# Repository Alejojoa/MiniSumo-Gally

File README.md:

# MiniSumo "Gally"                   
Mini sumo diseñado para competir en la LNR. 
Este repositorio contiene todas las piezas fabricables del Robot, y extras como soportes, versiones no finales del chasis, otros diseños de chasis, etc.

## ⚙️ Características 

- Tamaño: [10x10]
- Peso: [470g]
- Controlador: [Arduino Nano]
- Sensores:
  - Sensores de línea infrarrojos QRE-1113 x 2
  - Sensores JS40F x 4
- Motores: [Motores JSUMO CORE 400RPM]
- Batería: [Tattu 3S 450mAh]

# Pre Render del chasis final del robot.

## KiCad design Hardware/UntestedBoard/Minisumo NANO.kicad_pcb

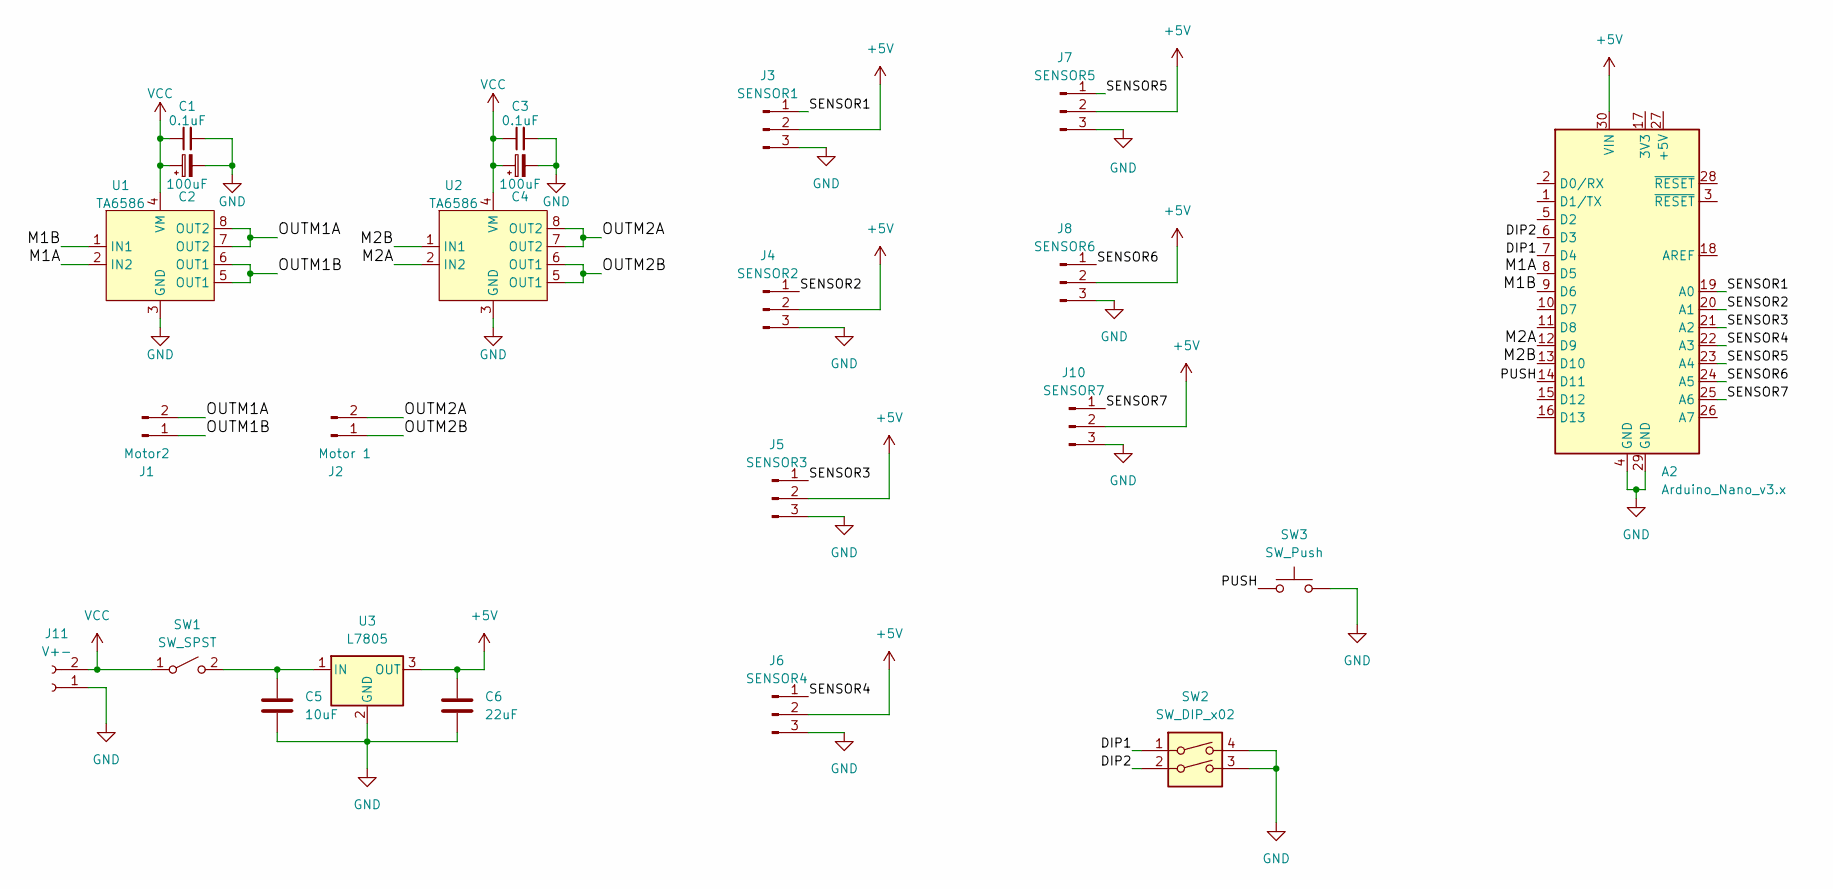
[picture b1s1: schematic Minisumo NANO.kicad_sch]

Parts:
A2: Arduino_Nano_v3.x; Arduino_Nano
C1, C3: 0.1uF; C_0805_2012Metric_Pad1.18x1.45mm_HandSolder
C2, C4: 100uF; CP_Radial_D5.0mm_P2.50mm
C5: 10uF; C_0805_2012Metric_Pad1.18x1.45mm_HandSolder
C6: 22uF; C_0805_2012Metric_Pad1.18x1.45mm_HandSolder
J1: Motor2; JST_XH_B2B-XH-A_1x02_P2.50mm_Vertical
J2: Motor 1; JST_XH_B2B-XH-A_1x02_P2.50mm_Vertical
J3: SENSOR1; PinHeader_1x03_P2.54mm_Vertical
J4: SENSOR2; PinHeader_1x03_P2.54mm_Vertical
J5: SENSOR3; PinHeader_1x03_P2.54mm_Vertical
J6: SENSOR4; PinHeader_1x03_P2.54mm_Vertical
J7: SENSOR5; PinHeader_1x03_P2.54mm_Vertical
J8: SENSOR6; PinHeader_1x03_P2.54mm_Vertical
J10: SENSOR7; PinHeader_1x03_P2.54mm_Vertical
J11: V+-; BORNERA2
SW1: SW_SPST; PinHeader_1x02_P2.54mm_Vertical
SW2: SW_DIP_x02; SW_DIP_SPSTx02_Slide_6.7x6.64mm_W7.62mm_P2.54mm_LowProfile
SW3: SW_Push; SW_PUSH_6mm_H5mm
U1, U2: TA6586; DIP-8_W7.62mm
U3: L7805; TO-220-3_Vertical

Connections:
+5V: A2.30 (VIN), C6.1, J3.2, J4.2, J5.2, J6.2, J7.2, J8.2, J10.2, U3.3 (OUT)
/DIP1: A2.7 (D4), SW2.1
/DIP2: A2.6 (D3), SW2.2
/M1A: A2.8 (D5), U1.2 (IN2)
/M1B: A2.9 (D6), U1.1 (IN1)
/M2A: A2.12 (D9), U2.2 (IN2)
/M2B: A2.13 (D10), U2.1 (IN1)
/OUTM1A: J1.2, U1.7 (OUT2), U1.8 (OUT2)
/OUTM1B: J1.1, U1.5 (OUT1), U1.6 (OUT1)
/OUTM2A: J2.2, U2.7 (OUT2), U2.8 (OUT2)
/OUTM2B: J2.1, U2.5 (OUT1), U2.6 (OUT1)
/PUSH: A2.14 (D11), SW3.1
/SENSOR1: A2.19 (A0), J3.1
/SENSOR2: A2.20 (A1), J4.1
/SENSOR3: A2.21 (A2), J5.1
/SENSOR4: A2.22 (A3), J6.1
/SENSOR5: A2.23 (A4), J7.1
/SENSOR6: A2.24 (A5), J8.1
/SENSOR7: A2.25 (A6), J10.1
GND: A2.4 (GND), A2.29 (GND), C1.2, C2.2, C3.2, C4.2, C5.2, C6.2, J3.3, J4.3, J5.3, J6.3, J7.3, J8.3, J10.3, J11.1, SW2.3, SW2.4, SW3.2, U1.3 (GND), U2.3 (GND), U3.2 (GND)
unnamed: C5.1, SW1.2 (B), U3.1 (IN)
VCC: C1.1, C2.1, C3.1, C4.1, J11.2, SW1.1 (A), U1.4 (VM), U2.4 (VM)

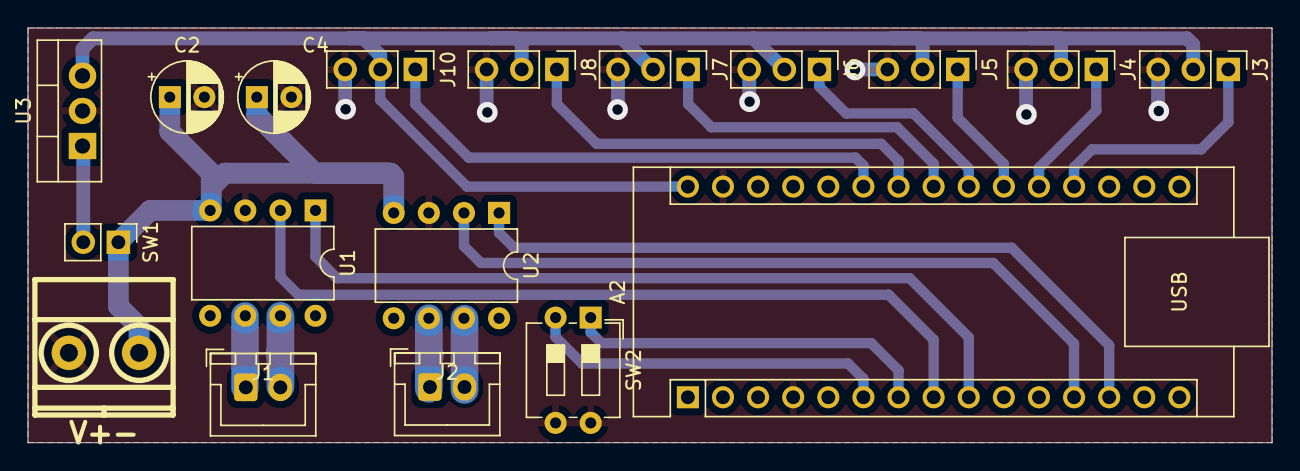
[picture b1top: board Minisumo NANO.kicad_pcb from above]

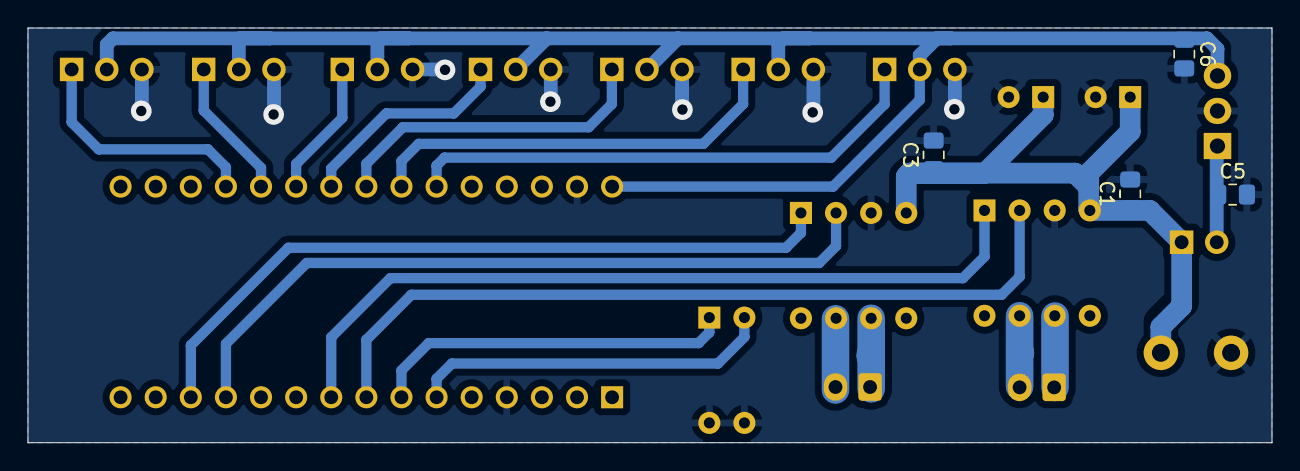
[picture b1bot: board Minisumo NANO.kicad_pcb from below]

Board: 2 copper layers, 90.0 x 30.0 mm, 22 parts (4 on the bottom side), 21 nets.

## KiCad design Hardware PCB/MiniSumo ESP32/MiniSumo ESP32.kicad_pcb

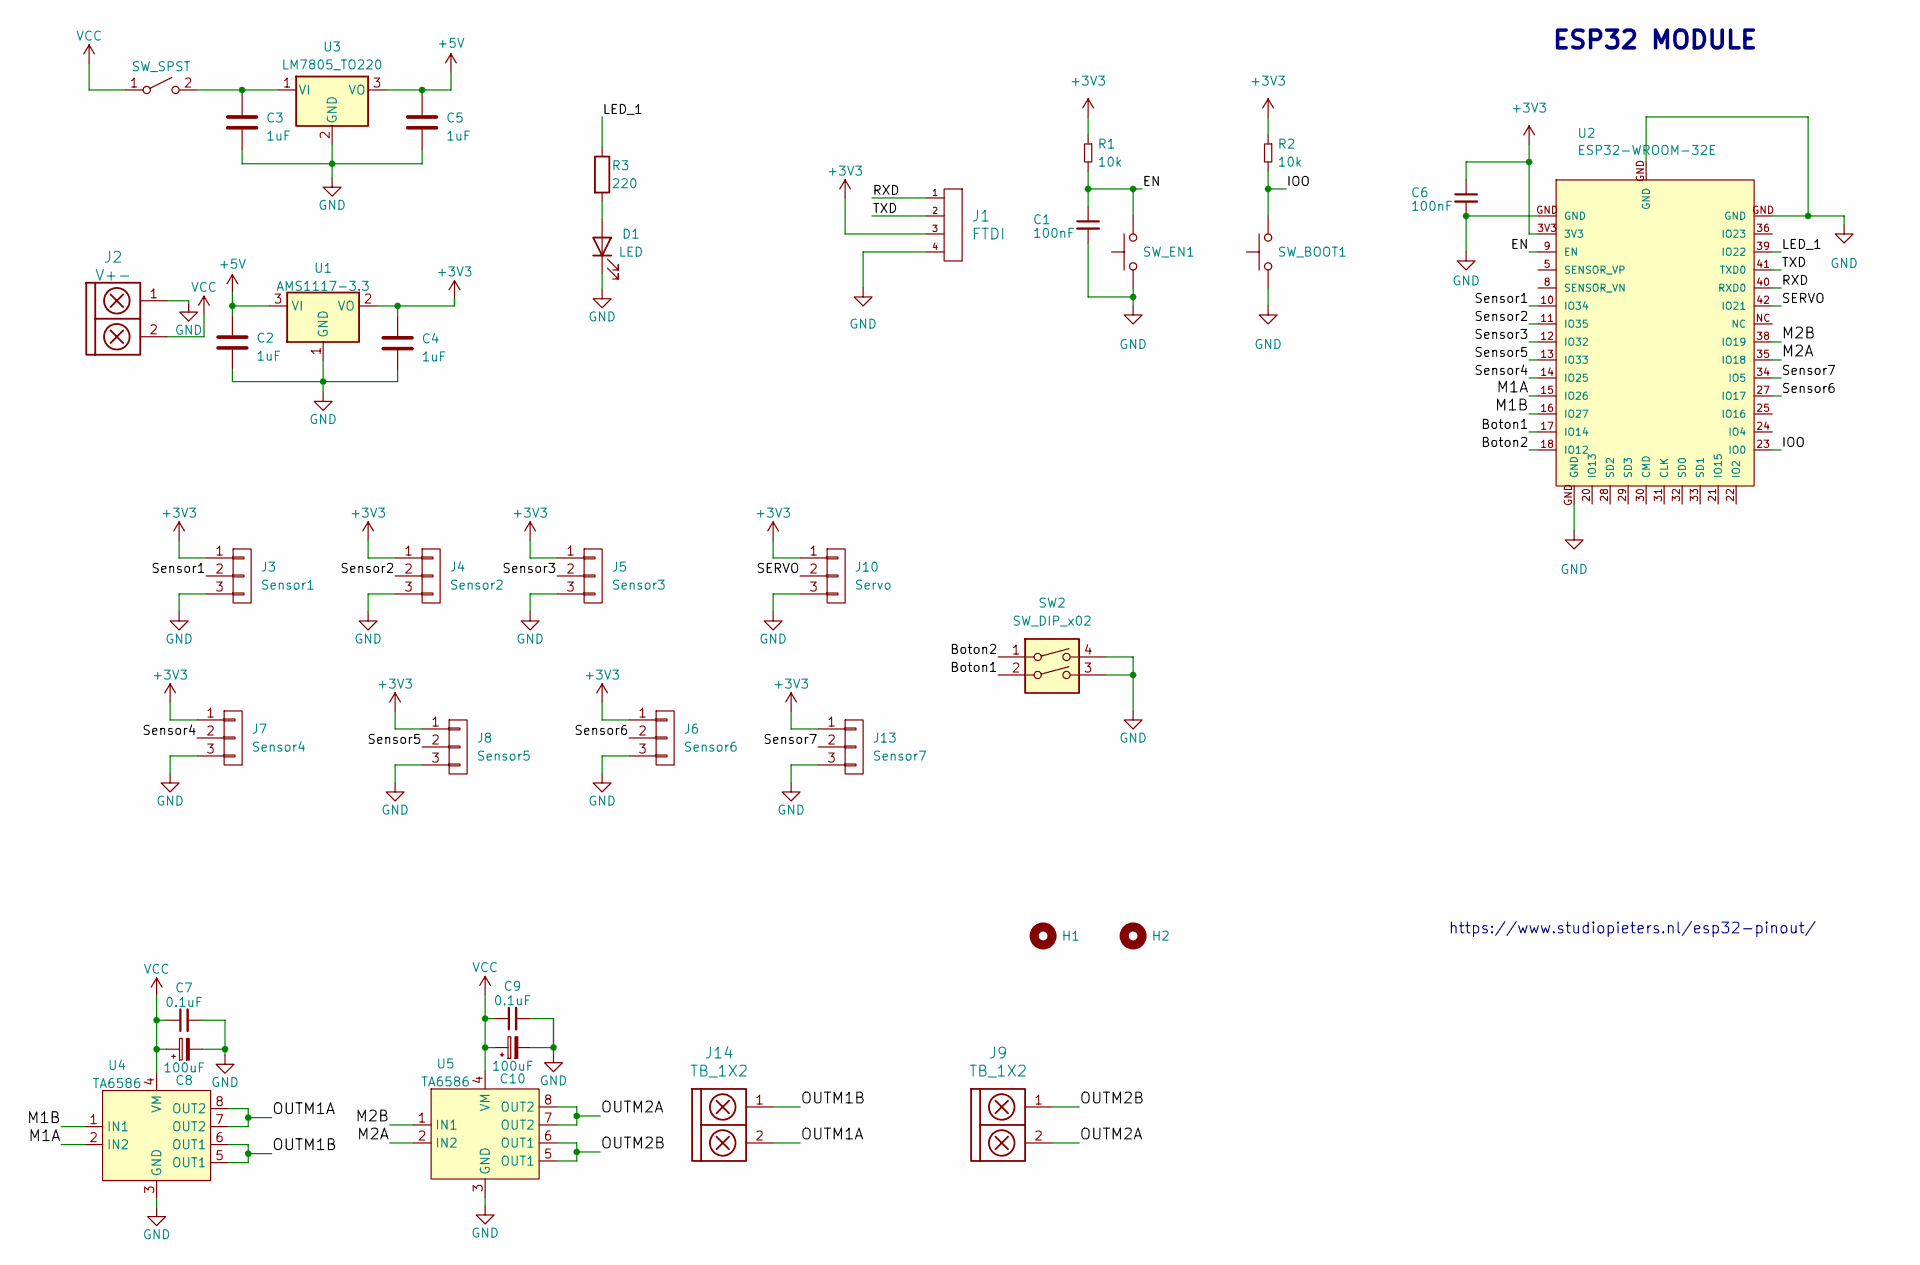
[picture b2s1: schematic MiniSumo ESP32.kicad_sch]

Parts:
C1, C6: 100nF; C_0805
C2, C3, C4, C5: 1uF; C_0805_2012Metric_Pad1.18x1.45mm_HandSolder
C7, C9: 0.1uF; C_0805
C8, C10: 100uF; CP_Radial_D5.0mm_P2.50mm
D1: LED; Led_0805
H1, H2: Mounting_Hole; hole_3mm
J1: FTDI; PinSocket_1x04_P2.54mm_Vertical
J2: V+-; BORNERA2_AZUL
J3: Sensor1; PinHeader_1x03_P2.54mm_Vertical
J4: Sensor2; PinHeader_1x03_P2.54mm_Vertical
J5: Sensor3; PinHeader_1x03_P2.54mm_Vertical
J6: Sensor6; PinHeader_1x03_P2.54mm_Vertical
J7: Sensor4; PinHeader_1x03_P2.54mm_Vertical
J8: Sensor5; PinHeader_1x03_P2.54mm_Vertical
J9, J14: TB_1X2; BORNERA2_AZUL
J10: Servo; PinHeader_1x03_P2.54mm_Vertical
J13: Sensor7; PinHeader_1x03_P2.54mm_Vertical
R1, R2: 10k; R_0805
R3: 220; R_1206
SW1: SW_SPST; PinHeader_1x02_P2.54mm_Vertical
SW2: SW_DIP_x02; SW_DIP_SPSTx02_Slide_6.7x6.64mm_W7.62mm_P2.54mm_LowProfile
SW_BOOT1: SW_Push; Pulsador_SMD_2_BAJO
SW_EN1: SW_Push; Pulsador_SMD_2_BAJO
U1: AMS1117-3.3; SOT-223-3_TabPin2
U2: ESP32-WROOM-32E
U3: LM7805_TO220; TO-220-3_Vertical
U4, U5: TA6586; DIP-8_W7.62mm

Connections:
+3V3: C4.1, C6.1, J1.3, J3.1, J4.1, J5.1, J6.1, J7.1, J8.1, J10.1, J13.1, R1.1, R2.1, U1.2 (VO), U2.3V3
+5V: C2.1, C5.1, U1.3 (VI), U3.3 (VO)
/Boton1: SW2.2, U2.17 (IO14)
/Boton2: SW2.1, U2.18 (IO12)
/EN: C1.1, R1.2, SW_EN1.2, U2.9 (EN)
/IOO: R2.2, SW_BOOT1.2, U2.23 (IO0)
/LED_1: R3.1, U2.39 (IO22)
/M1A: U2.15 (IO26), U4.2 (IN2)
/M1B: U2.16 (IO27), U4.1 (IN1)
/M2A: U2.35 (IO18), U5.2 (IN2)
/M2B: U2.38 (IO19), U5.1 (IN1)
/OUTM1A: J14.2, U4.7 (OUT2), U4.8 (OUT2)
/OUTM1B: J14.1, U4.5 (OUT1), U4.6 (OUT1)
/OUTM2A: J9.2, U5.7 (OUT2), U5.8 (OUT2)
/OUTM2B: J9.1, U5.5 (OUT1), U5.6 (OUT1)
/RXD: J1.1, U2.40 (RXD0)
/SERVO: J10.2, U2.42 (IO21)
/Sensor1: J3.2, U2.10 (IO34)
/Sensor2: J4.2, U2.11 (IO35)
/Sensor3: J5.2, U2.12 (IO32)
/Sensor4: J7.2, U2.14 (IO25)
/Sensor5: J8.2, U2.13 (IO33)
/Sensor6: J6.2, U2.27 (IO17)
/Sensor7: J13.2, U2.34 (IO5)
/TXD: J1.2, U2.41 (TXD0)
GND: C1.2, C2.2, C3.2, C4.2, C5.2, C6.2, C7.2, C8.2, C9.2, C10.2, D1.1 (K), J1.4, J2.1, J3.3, J4.3, J5.3, J6.3, J7.3, J8.3, J10.3, J13.3, SW2.3, SW2.4, SW_BOOT1.1, SW_EN1.1, U1.1 (GND), U2.GND, U3.2 (GND), U4.3 (GND), U5.3 (GND)
unnamed: D1.2 (A), R3.2
unnamed: C3.1, SW1.2 (B), U3.1 (VI)
VCC: C7.1, C8.1, C9.1, C10.1, J2.2, SW1.1 (A), U4.4 (VM), U5.4 (VM)

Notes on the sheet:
ESP32 MODULE
https://www.studiopieters.nl/esp32-pinout/

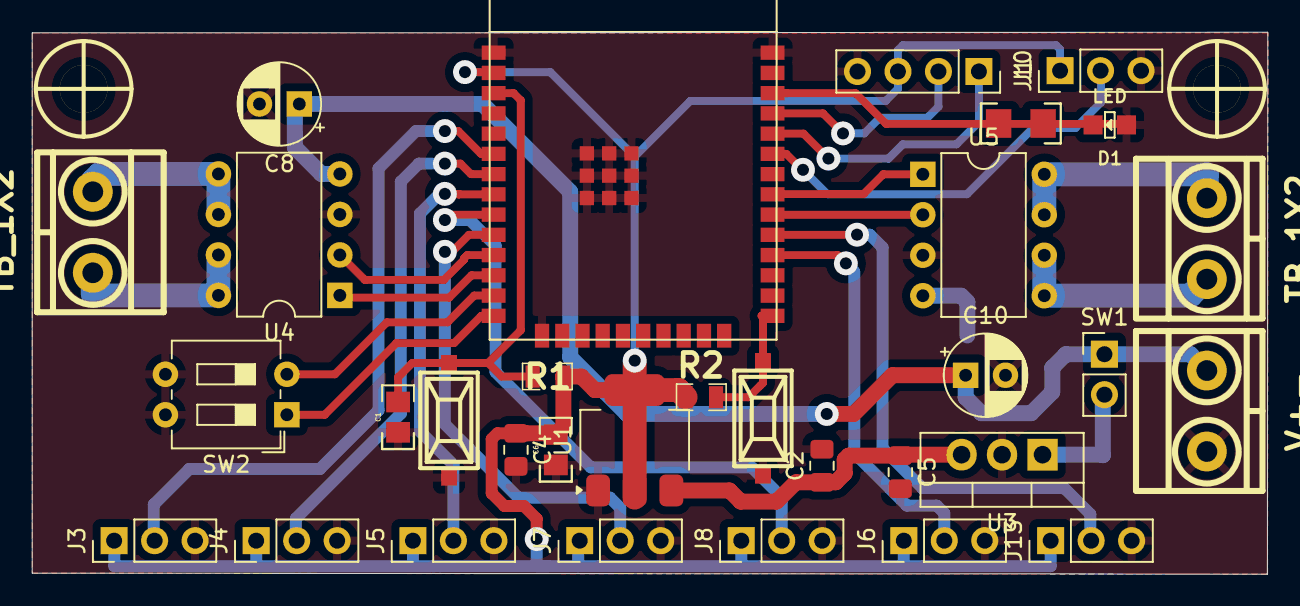
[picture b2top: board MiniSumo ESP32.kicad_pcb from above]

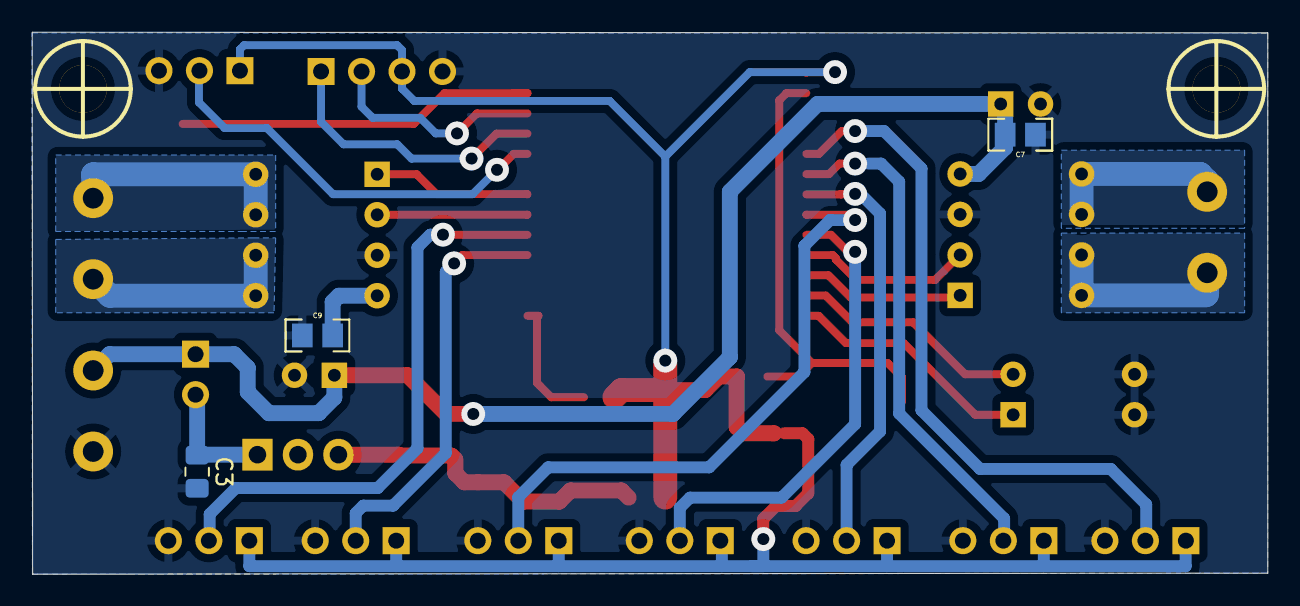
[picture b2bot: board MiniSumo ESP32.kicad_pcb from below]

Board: 2 copper layers, 77.5 x 34.0 mm, 37 parts (3 on the bottom side), 29 nets.

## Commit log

2025-05-16 Update README.md
    xd
